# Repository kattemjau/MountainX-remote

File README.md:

# MountainX-remote
PCB of remote, designed in Kicad
Inspired by Adafruit, and SolidGeek

https://learn.adafruit.com/bluefruit-nrf52-feather-learning-guide?view=all#downloads

https://www.electric-skateboard.builders/t/simple-3d-printed-nrf-remote-arduino-controlled/28543

V3 is not yet tested

Arduino compadible CODE can be found here:
https://github.com/Heplaphon/MountainX-Remote

Follow setupguide from Adafruit: https://learn.adafruit.com/bluefruit-nrf52-feather-learning-guide?view=all#arduino-bsp-setup

V2 up and working with Arduino IDE, can be programmed over USB, JTAG and OTA (bluetooth)

3D model of PCB can be found here:
https://github.com/kattemjau/MountainX-remote/tree/master/3D%20model

3D model of remote can be found here:
https://github.com/kattemjau/MountainX-remote/tree/master/3D%20model/V2

Images can be found here:
https://github.com/kattemjau/MountainX-remote/tree/master/Images

Features:

3 Hall sensors for more accurate readings, 
Nordic NRF52 Bluetooth 5, Arm Cotex m4,
Oled screen with telematry from Vesc: Speed, distance, battery voltage, error codes e.t.c, 
Remote battery reading, 
1A Fast charger, 
Long battery life, 
Dual battery to prevent battery disconnect due to shaking, 
Spring loaded knob and trigger, 
Deadmans switch, 
Opensource reprogrammable firmware with arduino IDE, 
Connects with up to 20 clients, long range and high bandwidth,

Changes:

3D model now available, 
Integrated OLED screen, 
Correct angles on Hall sensors, 
Extra battery plug, 
More leds, 
More decoupling caps, 
Better layout, 
Changes to footprints, 
NOW USB C, 

Note:
Jtag programming header is mirrored, just flip the cable to get it to work. "Jtag is not needed"
https://shop-us.segger.com/J_Link_EDU_mini_p/8.08.91.htm

Footprint for Raytac NRF52832 not correct, and SS12D11 (SWITCH) is missing

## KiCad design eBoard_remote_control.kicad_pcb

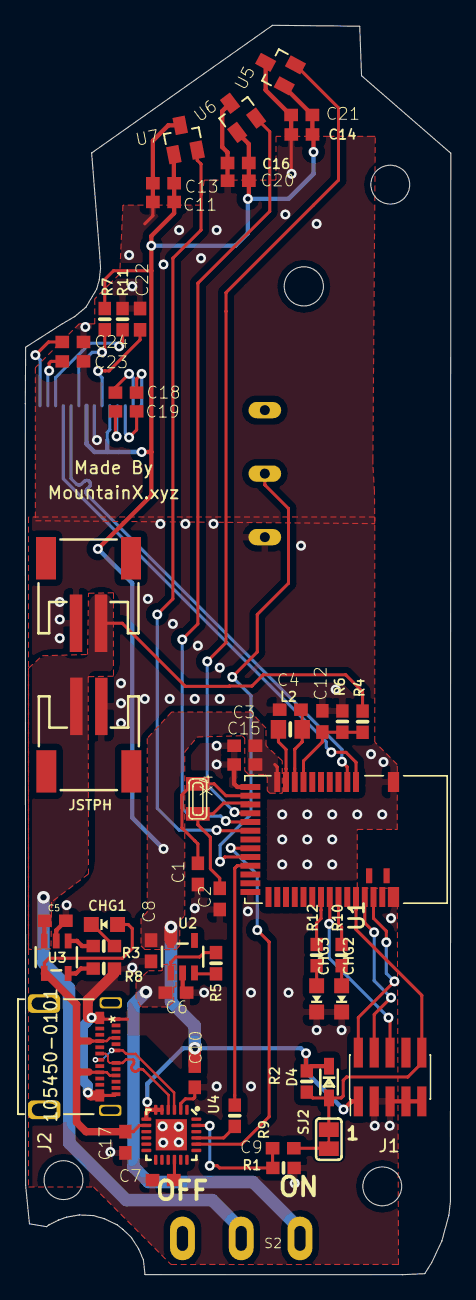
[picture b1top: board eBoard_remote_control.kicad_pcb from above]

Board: 2 copper layers, 34.0 x 99.9 mm, 57 parts (0 on the bottom side), 45 nets.

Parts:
C1, C2: 22pF; C0603
C3, C23, C24: 10uF; C0603
C4, C18, C19, C22: 1uF; C0603
C5, C6, C8, C11, C14, C17, C20: 10µF; C0603
C7: 10uf; C0603
C9, C10: 0.1uF; C0603
C12: 1nF; C0603
C13, C15, C16, C21: 100nF; C0603
CHG1, CHG2, CHG3: BLUE; CHIPLED_0805_NOOUTLINE
D4: 1n4148; SOD-323
J1: SWDIO_conn; PinHeader_2x05_P1.27mm_Vertical_SMD
J2: 105450-0101
L2: 10uH; 0805-NO
R1, R3, R8, R9, R10, R12: 1K; 0603-NO
R2, R7: 10K; 0603-NO
R4: 806K; 0603-NO
R5: 100K; 0603-NO
R6: 2M; 0603-NO
R11: 390k; 0603-NO
S1: K9-1267B-L
S2: SS12D11
SJ2: BAT; SOLDERJUMPER_CLOSEDWIRE
U1: MDBT42; BLE_MODULE_RAYTAC_MDBT42
U2: AP2112(3.3V); SOT23-5
U3: MCP73831T-2ACI/OT; SOT23-5
U4: CP2104; QFN24_4MM_SMSC
U5, U6, U7: AH49ENTR-G1; SOT23
U8: SSD1306; SSD1306_OLED-0.91-128x32
X1, X2: JSTPH; JSTPH2
X4: 32.768; XTAL3215

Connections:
3.3V: C3.1, C8.1, C10.1, C11.1, C13.1, C14.1, C15.1, C16.1, C20.1, C21.1, D4.C, J1.1, R2.1, R7.2, U1.11, U2.5, U4.5, U4.6, U4.7, U5.1, U6.1, U7.1, U8.5, U8.8
/A0: U1.15, U5.2
/A1: U1.16, U6.2
/A2: U1.17, U7.2
/A7/P0.31: C12.1, R4.2, R6.1, U1.8
/DTR: C9.2, R1.2, U4.23
/P0.07: S1.P2, U1.20
/RESET: D4.A, J1.10, R2.2, SJ2.2, U1.35
/RXD: R9.2, U1.21
/SWCLK: J1.4, U1.36
/SWDIO: J1.2, U1.37
/SWO: J1.6, U1.32
/TXD: U1.19, U4.20
/VBB: C6.1, R5.2, S2.1, U2.1
GND: C1.2, C2.2, C3.2, C4.2, C5.2, C6.2, C7.2, C8.2, C10.2, C11.2, C12.2, C13.2, C14.2, C15.2, C16.2, C17.2, C20.2, C21.2, C22.1, C23.1, C24.1, CHG2.C, CHG3.C, J1.3, J1.5, J1.7, J1.9, J2.A1, J2.A12, J2.B1, J2.B12, R1.1, R6.2, R8.2, R11.2, S1.P1, U1.1, U1.12, U1.24, U1.39, U2.2, U3.2, U4.2, U4.THERM, U5.3, U6.3, U7.3, U8.7, X1.1, X2.1
unnamed: C1.1, U1.13, X4.P$1
unnamed: C2.1, U1.14, X4.P$2
unnamed: C4.1, L2.1, U1.9
unnamed: C7.1, U4.16
unnamed: C9.1, SJ2.1
unnamed: C18.1, U8.1
unnamed: C18.2, U8.2
unnamed: C19.1, U8.3
unnamed: C19.2, U8.4
unnamed: C22.2, U8.6
unnamed: C23.2, U8.13
unnamed: C24.2, U8.14
unnamed: CHG1.C, R3.1
unnamed: CHG2.A, R10.1
unnamed: CHG3.A, R12.1
unnamed: L2.2, U1.10
unnamed: R3.2, U3.1
unnamed: R5.1, U2.3
unnamed: R7.1, U8.9
unnamed: R8.1, U3.5
unnamed: R9.1, U4.21
unnamed: R10.2, U1.33
unnamed: R11.1, U8.12
unnamed: R12.2, U1.31
SCL: U1.3, U8.10
SDA: U1.2, U8.11
USBD+: J2.A6, J2.B6, U4.3
USBD-: J2.A7, J2.B7, U4.4
VBAT: C5.1, R4.1, S2.2, U3.3, X1.2, X2.2
VBUS: C17.1, CHG1.A, J2.A4, J2.A9, J2.B4, J2.B9, U3.4, U4.8

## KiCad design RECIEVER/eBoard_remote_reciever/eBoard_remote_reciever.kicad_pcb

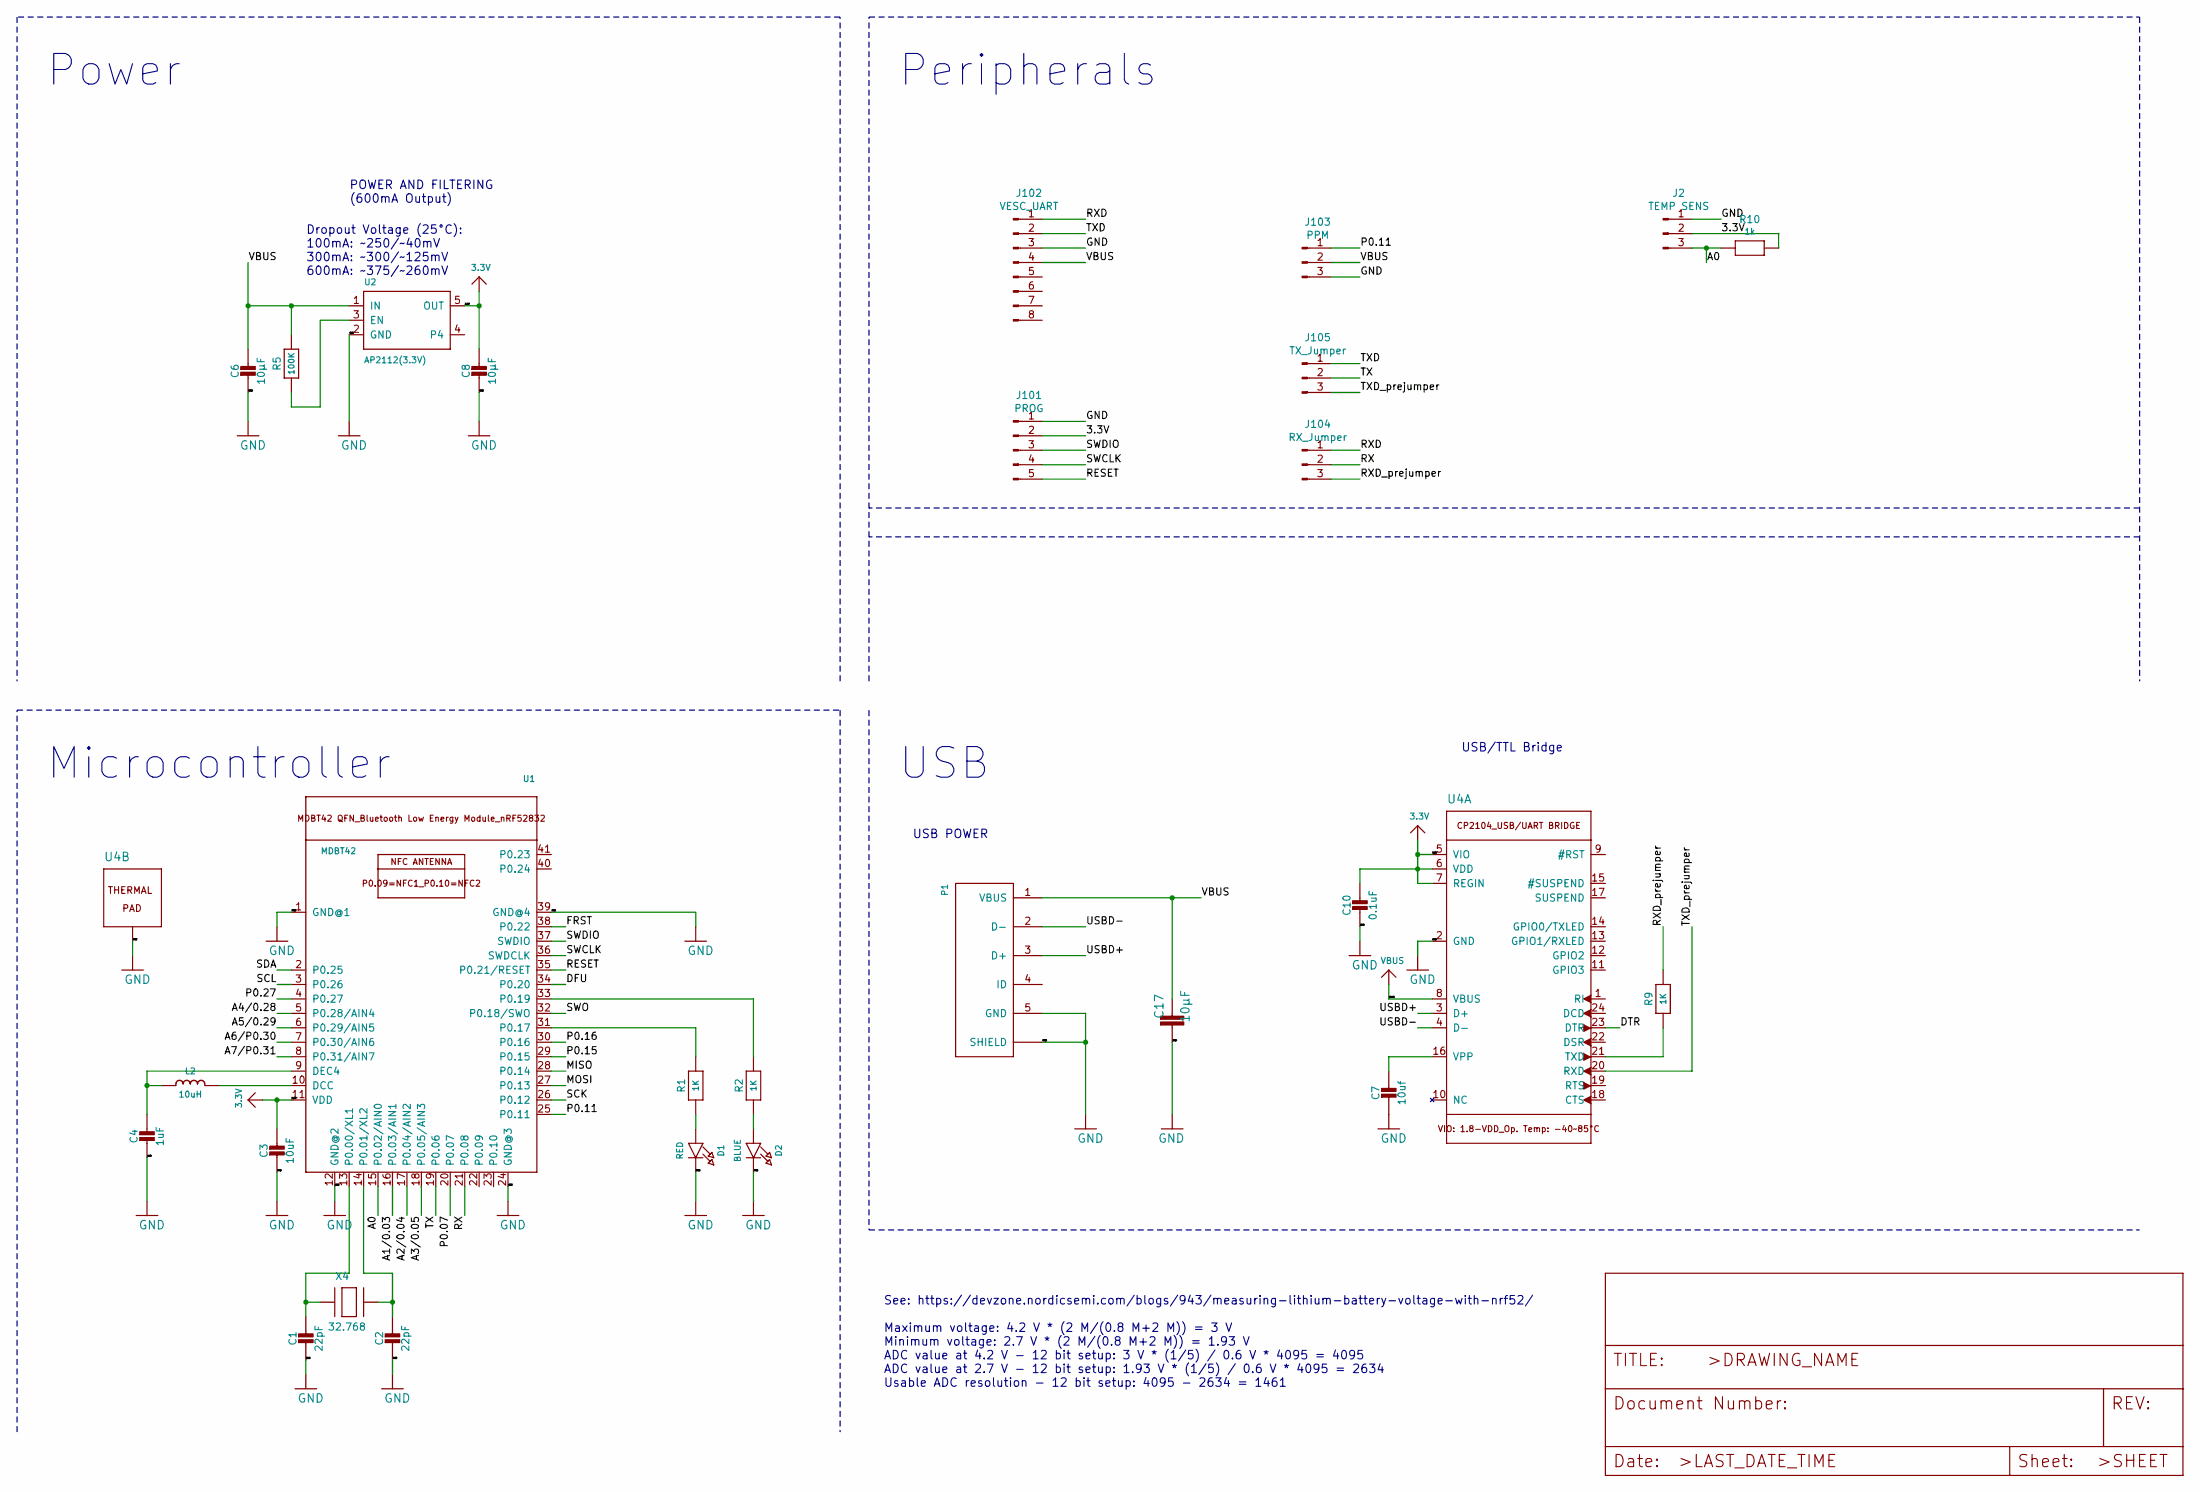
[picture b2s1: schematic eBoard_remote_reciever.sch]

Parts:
C1, C2: 22pF; 0603-NO
C3: 10uF; 0805-NO
C4: 1uF; 0603-NO
C6, C8: 10µF; 0805-NO
C7: 10uf; 0805-NO
C10: 0.1uF; 0603-NO
C17: 10µF; C0603
D1: RED; D_0805_2012Metric
D2: BLUE; D_0805_2012Metric
J2: TEMP SENS; PinHeader_1x03_P2.54mm_Vertical
J101: PROG; PinHeader_1x05_P2.54mm_Vertical
J102: VESC_UART; PinHeader_1x09_P2.54mm_Vertical
J103: PPM; PinHeader_1x03_P2.54mm_Vertical
J104: RX_Jumper; PinHeader_1x03_P2.54mm_Vertical
J105: TX_Jumper; PinHeader_1x03_P2.54mm_Vertical
L2: 10uH; 0805-NO
P1: USB; USB-MICRO-B
R1, R2, R9: 1K; 0603-NO
R5: 100K; 0603-NO
R10: 1k; R_0603_1608Metric
U1: MDBT42; BLE_MODULE_RAYTAC_MDBT42
U2: AP2112(3.3V); SOT23-5
U4: CP2104; QFN24_4MM_SMSC
X4: 32.768; XTAL3215

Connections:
3.3V: C3.1, C8.1, C10.1, J2.2, J101.2, R10.1, U1.11 (VDD), U2.5 (OUT), U4.5 (VIO), U4.6 (VDD), U4.7 (REGIN)
/A0: J2.3, R10.2, U1.15 (P0.02/AIN0)
/A1/0.03: U1.16 (P0.03/AIN1)
/A2/0.04: U1.17 (P0.04/AIN2)
/A3/0.05: U1.18 (P0.05/AIN3)
/A4/0.28: U1.5 (P0.28/AIN4)
/A5/0.29: U1.6 (P0.29/AIN5)
/A6/P0.30: U1.7 (P0.30/AIN6)
/A7/P0.31: U1.8 (P0.31/AIN7)
/DFU: U1.34 (P0.20)
/DTR: U4.23 (DTR)
/FRST: U1.38 (P0.22)
/MISO: U1.28 (P0.14)
/MOSI: U1.27 (P0.13)
/P0.07: U1.20 (P0.07)
/P0.11: J103.1, U1.25 (P0.11)
/P0.15: U1.29 (P0.15)
/P0.16: U1.30 (P0.16)
/P0.27: U1.4 (P0.27)
/RESET: J101.5, U1.35 (P0.21/RESET)
/RX: J104.2, U1.21 (P0.08)
/RXD: J102.1, J104.1
/RXD_prejumper: J104.3, R9.2
/SCK: U1.26 (P0.12)
/SCL: U1.3 (P0.26)
/SDA: U1.2 (P0.25)
/SWCLK: J101.4, U1.36 (SWDCLK)
/SWDIO: J101.3, U1.37 (SWDIO)
/SWO: U1.32 (P0.18/SWO)
/TX: J105.2, U1.19 (P0.06)
/TXD: J102.2, J105.1
/TXD_prejumper: J105.3, U4.20 (RXD)
/USBD+: P1.3 (D+), U4.3 (D+)
/USBD-: P1.2 (D-), U4.4 (D-)
GND: C1.2, C2.2, C3.2, C4.2, C6.2, C7.2, C8.2, C10.2, C17.2, D1.C, D2.C, J2.1, J101.1, J102.3, J103.3, P1.5 (GND), P1.G1 (SHIELD), P1.G2 (SHIELD), P1.G3 (SHIELD), P1.G4 (SHIELD), U1.1 (GND@1), U1.12 (GND@2), U1.24 (GND@3), U1.39 (GND@4), U2.2 (GND), U4.2 (GND), U4.THERM (TP)
unnamed: C1.1, U1.13 (P0.00/XL1), X4.P$1
unnamed: C2.1, U1.14 (P0.01/XL2), X4.P$2
unnamed: C4.1, L2.1, U1.9 (DEC4)
unnamed: C7.1, U4.16 (VPP)
unnamed: D1.A, R1.1
unnamed: D2.A, R2.1
unnamed: L2.2, U1.10 (DCC)
unnamed: R1.2, U1.31 (P0.17)
unnamed: R2.2, U1.33 (P0.19)
unnamed: R5.1, U2.3 (EN)
unnamed: R9.1, U4.21 (TXD)
VBUS: C6.1, C17.1, J102.4, J103.2, P1.1 (VBUS), R5.2, U2.1 (IN), U4.8 (VBUS)

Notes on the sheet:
POWER AND FILTERING (600mA Output)
Dropout Voltage (25°C): 100mA: ~~250/~~40mV 300mA: ~~300/~~125mV 600mA: ~~375/~~260mV
USB POWER
USB/TTL Bridge
See: https://devzone.nordicsemi.com/blogs/943/measuring-lithium-battery-voltage-with-nrf52/ Maximum voltage: 4.2 V * (2 M/(0.8 M+2 M)) = 3 V Minimum voltage: 2.7 V * (2 M/(0.8 M+2 M)) = 1.93 V ADC value at 4.2 V - 12 bit setup: 3 V * (1/5) / 0.6 V * 4095 = 4095 ADC value at 2.7 V - 12 bit setup: 1.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
Power
Peripherals
Microcontroller
USB

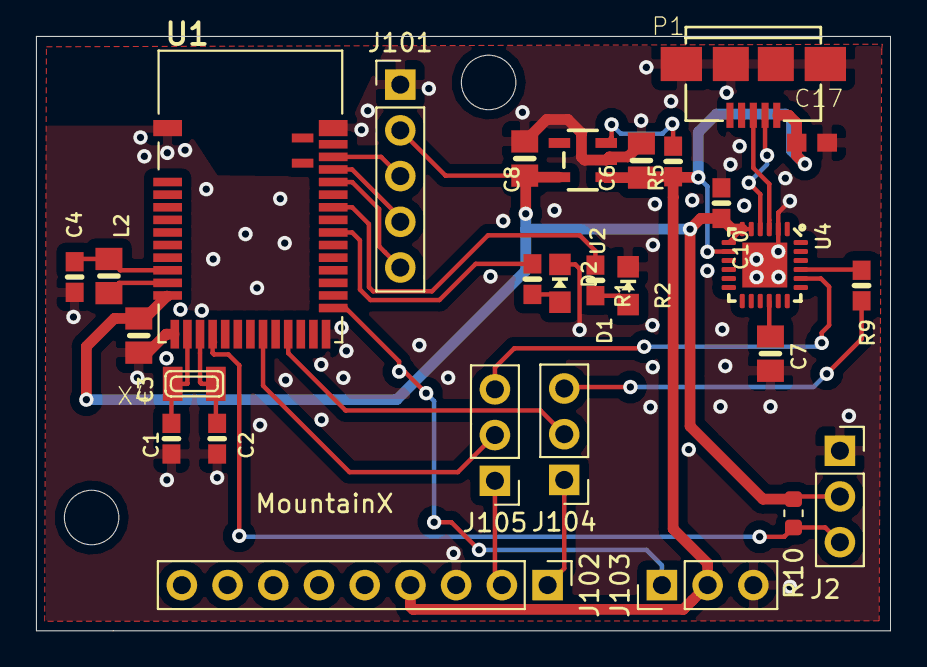
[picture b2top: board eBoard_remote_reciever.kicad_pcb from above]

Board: 2 copper layers, 47.4 x 33.0 mm, 28 parts (0 on the bottom side), 27 nets.

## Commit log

2019-01-08 V2 update
2019-04-18 V2.1
2019-04-23 this
2019-04-23 added dual jst and 3d models
2019-04-23 oled schem
2019-04-24 started Layout V3
2019-04-24 added rgb led V3
2019-04-27 updated 3d modelis
2019-04-29 Added 3D models
2019-04-29 more pics
2019-04-30 Create LICENSE

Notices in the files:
parts and their libraries:
Copyright 2016 Accelerated Designs. All rights reserved.
